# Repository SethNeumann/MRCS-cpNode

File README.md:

# MRCS-cpNode
## License: Creative Commons Attribution-NonCommercial-ShareAlike

cpNode and I/O expander (IOX) boards have been updated to version
2.6. Based on customer feedback, and our design and installation
experience, the changes were made to provide more efficient and
flexible physical layout of some components.

  * Rev 2.6 boards are 100% backward compatible with current versions. No software changes are needed.

Version 2.6 brings the following improvements to the proven cpNode design:

  * CMRInet interface connection has been made consistent with five position pads (R+, R-,T+,T-,SHLD).for 3.5mm screw terminals, we've removed some rarely used configurations
  * Input/Output pads moved .2" back from edge for better DIN rail clearance. The I/O option pad area accepts standard DIP component headers with 0.4" pad spacing.
  * Gnd/LED Com pads aligned to .1" (2.54 mm) for a screw terminal block or male header pins
  * Removed rarely ordered on board stall motor driver option

What does a cpNode do?

cpNodes provide input and output (I/O) ports which connect to LEDs
for signals, push buttons, turnout motors, block detectors, and
other devices to a central computer for controlling model railroads.
cpNodes may also be used as standalone controllers for staging,
crossings and interlocking plants.

You must provide a Bread Board Leonardo (BB-Leo) processor, available
from Modern Device, use coupon code "cpnode"  (DO NOT order the
header kit as headers for the BB-Leo are included in all assembled
cpNode configurations.) or order the "cpNode 2.5 LE" which includes
the BB-Leo

A cpNode has:

  * 16 I/O lines with solder pads for LED limiting resistors
  * Screw terminal blocks or solder pads to connect external devices - see configurations below
  * CMRInet RS-422/485 Network Interface.  CMRInet is now NMRA Layout Control Specification S9-10
  * I2C interface for adding Input/Output Expander (IOX) boards for more i/o ports
  * All the i/o needed to control one end of a CTC siding, just add signals and detectors and switch motor drivers
  * Female headers to receive a BB-Leo (Arduino) processor available from Modern Device, use coupon code "cpnode" or order the cpNode LE option
  * I/O is configured in 8 bit groups, providing up to 144 lines when fully expanded with IOX16s and/or IOX32s
  * Use cpNodes as small, economical, CMRI nodes as is or customize the code to support applications requiring local intelligence
  * BB-Leo uses the Atmel Atmega32u4 processor chip, see the data sheet for electrical characteristics
  * Standard "Sketch" (Arduino program) is compatible with JMRI or traditional CMRI BASIC/Visual Basic development tools

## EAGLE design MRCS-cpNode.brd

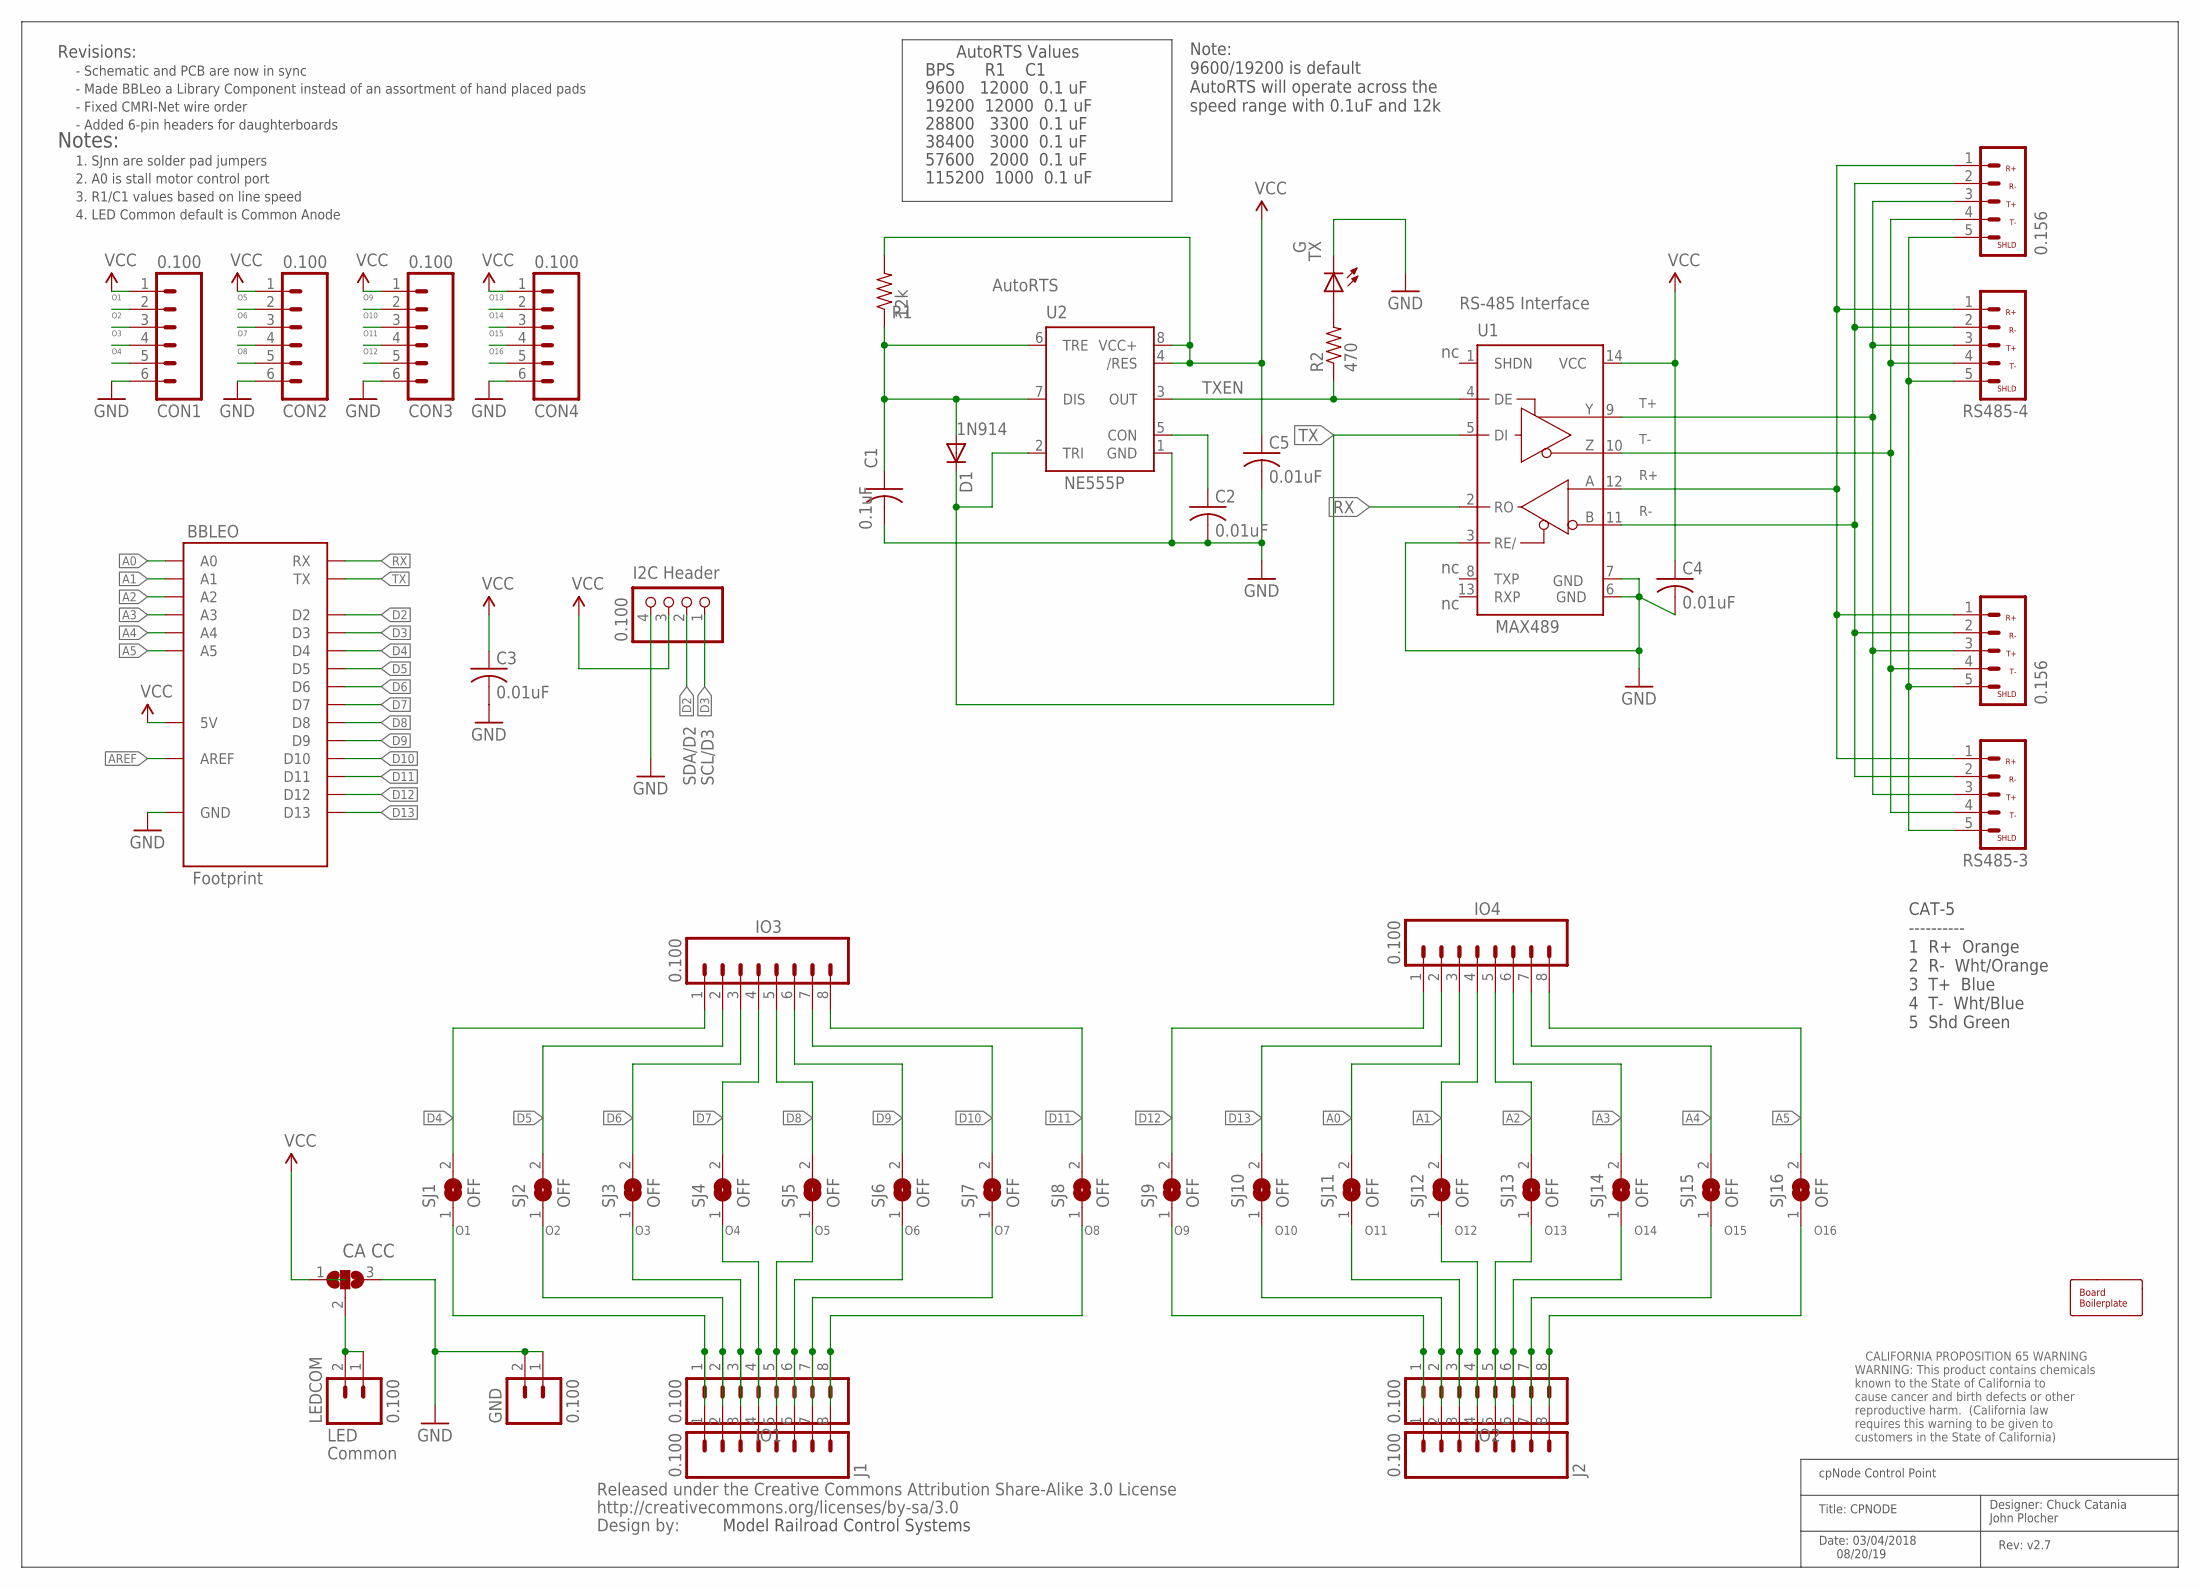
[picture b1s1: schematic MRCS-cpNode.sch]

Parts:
BBLEO: Footprint; ARDUINO-BBLEO
BOARD1: BOARD; BOARD-DINRAIL-2.71IN-MRCS
C1: 0.1uF; C-PTH-0.100
C2, C3, C4, C5: 0.01uF; C-PTH-0.100
CON1, CON2, CON3, CON4: 0.100; 1X06-SIP_LOCK
D1: 1N4148; DIODE-1N4148
GND: 0.100; MOLEX-1X2_LOCK
I2CHDR: 0.100; 1X04/90
IO1, IO2, IO3, IO4: 0.100; 1X08
J1, J2: 0.100; 1X08_LOCK_LONGPADS
LEDCOM: 0.100; MOLEX-1X2_LOCK
P1: CA CC; 3P-SMD-2X4.8
R1: 12k; AXIAL-0.4-RES
R2: 470; AXIAL-0.4-RES
RS485-1, RS485-2: 0.156; KK-156-5
RS485-3, RS485-4: 3.5mm; CMRINET-3.5MM
SJ1, SJ2, SJ3, SJ4, SJ5, SJ6, SJ7, SJ8, SJ9, SJ10, SJ11, SJ12, SJ13, SJ14, SJ15, SJ16: OFF; SJ
TX: G; LED3MM
U1: MAX3465CPD; DIL14
U2: NE555P; DIL-08
U$1: CREATIVE_COMMONS
U$2: Prop65; CA-PROP65WARNING

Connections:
A0: BBLEO.A0, IO4.3, SJ11.2
A1: BBLEO.A1, IO4.4, SJ12.2
A2: BBLEO.A2, IO4.5, SJ13.2
A3: BBLEO.A3, IO4.6, SJ14.2
A4: BBLEO.A4, IO4.7, SJ15.2
A5: BBLEO.A5, IO4.8, SJ16.2
AREF: BBLEO.AR (AREF)
D2: BBLEO.SDA (D2), I2CHDR.2
D3: BBLEO.SCL (D3), I2CHDR.1
D4: BBLEO.D4, IO3.1, SJ1.2
D5: BBLEO.D5, IO3.2, SJ2.2
D6: BBLEO.D6, IO3.3, SJ3.2
D7: BBLEO.D7, IO3.4, SJ4.2
D8: BBLEO.D8, IO3.5, SJ5.2
D9: BBLEO.D9, IO3.6, SJ6.2
D10: BBLEO.D10, IO3.7, SJ7.2
D11: BBLEO.D11, IO3.8, SJ8.2
D12: BBLEO.D12, IO4.1, SJ9.2
D13: BBLEO.D13, IO4.2, SJ10.2
GND: BBLEO.GND@0 (GND), BBLEO.GND@1 (GND), BBLEO.GND@2 (GND), BBLEO.GND@3 (GND), BBLEO.GND@4 (GND), C1.2, C2.2, C3.2, C4.2, C5.2, CON1.6, CON2.6, CON3.6, CON4.6, GND.1, GND.2, I2CHDR.4, P1.3, TX.K (C), U1.3 (RE/), U1.6 (GND), U1.7 (GND), U2.1 (GND)
unnamed: R2.P$2 (2), TX.A
unnamed: C2.1, U2.5 (CON)
unnamed: LEDCOM.1, LEDCOM.2, P1.2
unnamed: C1.1, D1.A, R1.P$1 (1), U2.6 (TRE), U2.7 (DIS)
unnamed: R2.P$1 (1), U1.4 (DE), U2.3 (OUT)
O1: CON1.2, IO1.1, J1.1, SJ1.1
O2: CON1.3, IO1.2, J1.2, SJ2.1
O3: CON1.4, IO1.3, J1.3, SJ3.1
O4: CON1.5, IO1.4, J1.4, SJ4.1
O5: CON2.2, IO1.5, J1.5, SJ5.1
O6: CON2.3, IO1.6, J1.6, SJ6.1
O7: CON2.4, IO1.7, J1.7, SJ7.1
O8: CON2.5, IO1.8, J1.8, SJ8.1
O9: CON3.2, IO2.1, J2.1, SJ9.1
O10: CON3.3, IO2.2, J2.2, SJ10.1
O11: CON3.4, IO2.3, J2.3, SJ11.1
O12: CON3.5, IO2.4, J2.4, SJ12.1
O13: CON4.2, IO2.5, J2.5, SJ13.1
O14: CON4.3, IO2.6, J2.6, SJ14.1
O15: CON4.4, IO2.7, J2.7, SJ15.1
O16: CON4.5, IO2.8, J2.8, SJ16.1
R+: RS485-1.1, RS485-2.1, RS485-3.1, RS485-4.1, U1.12 (A)
R-: RS485-1.2, RS485-2.2, RS485-3.2, RS485-4.2, U1.11 (B)
RX: BBLEO.RX, U1.2 (RO)
SHIELD: RS485-1.5, RS485-2.5, RS485-3.5, RS485-4.5
T+: RS485-1.3, RS485-2.3, RS485-3.3, RS485-4.3, U1.9 (Y)
T-: RS485-1.4, RS485-2.4, RS485-3.4, RS485-4.4, U1.10 (Z)
TX: BBLEO.TX, D1.C, U1.5 (DI), U2.2 (TRI)
VCC: BBLEO.+5V@1 (5V), BBLEO.+5V@2 (5V), BBLEO.+5V@3 (5V), BBLEO.+5V@4 (5V), C3.1, C4.1, C5.1, CON1.1, CON2.1, CON3.1, CON4.1, I2CHDR.3, P1.1, R1.P$2 (2), U1.14 (VCC), U2.4 (/RES), U2.8 (VCC+)

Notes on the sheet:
Rev: v2.7
Date: 03/04/2018 08/20/19
Title: CPNODE
cpNode Control Point
Designer: Chuck Catania John Plocher
SDA/D2
SCL/D3
TXEN
LED
1N914
MAX489
RS-485 Interface
Notes:
1. SJnn are solder pad jumpers
2. A0 is stall motor control port
I2C Header
3. R1/C1 values based on line speed
AutoRTS
AutoRTS Values
9600 12000 0.1 uF
19200 12000 0.1 uF
38400 3000 0.1 uF
57600 2000 0.1 uF
115200 1000 0.1 uF
BPS R1 C1
Common
4. LED Common default is Common Anode
Model Railroad Control Systems
Revisions:
CAT-5 ---------- 1 R+ Orange 2 R- Wht/Orange 3 T+ Blue 4 T- Wht/Blue 5 Shd Green
28800 3300 0.1 uF
Note: 9600/19200 is default AutoRTS will operate across the speed range with 0.1uF and 12k
- Fixed CMRI-Net wire order
- Schematic and PCB are now in sync
- Made BBLeo a Library Component instead of an assortment of hand placed pads
- Added 6-pin headers for daughterboards

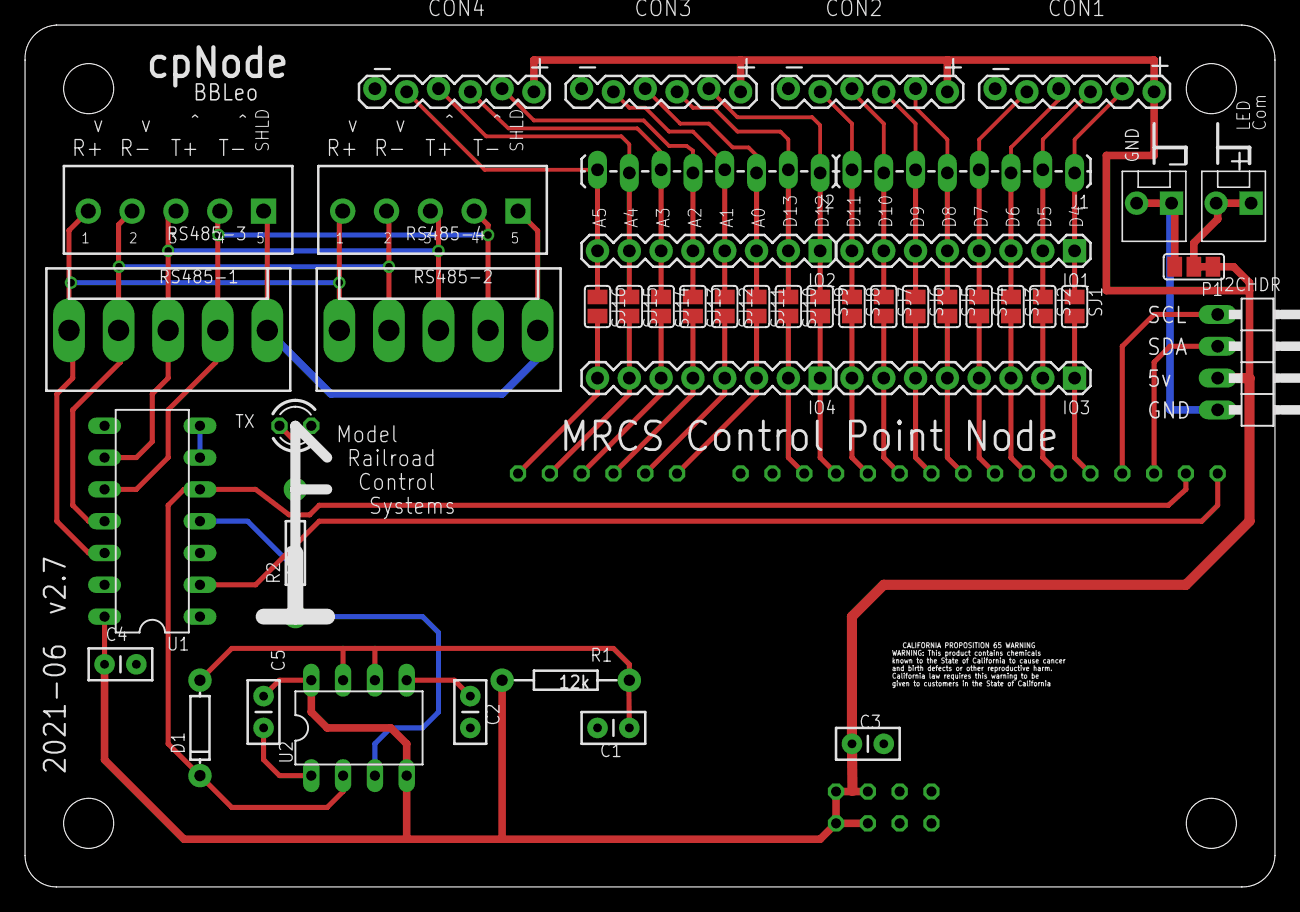
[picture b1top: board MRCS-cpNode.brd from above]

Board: 2 copper layers, 99.8 x 68.8 mm, 50 parts (0 on the bottom side), 48 nets.

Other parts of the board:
U$3: MRCS; MRCS-LOGO

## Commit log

2019-11-30 updated context
2019-11-30 Added metadata files
2019-12-09 project file names must be same as repo name
2020-01-22 added 6-pin headers, fixed DCR errors
2020-05-04 updated tags
2020-10-05 added missing values
2020-10-06 normalized values
2020-12-04 minor wording changes to effect version 2.6
    2.6 is a few of minor changes for EAGLE consistency. No I am slowly converting to some internal standards for easier maintenance in the future.
2021-03-02 rebuilding this repository
    added BOM and the last successful zip file
2021-06-03 silk and trace cleanup
2021-06-03 silk cleanuo

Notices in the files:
parts and their libraries:
SparkFun: Released under the Creative Commons Attribution Share-Alike 3.0 License
SparkFun: http://creativecommons.org/licenses/by-sa/3.0
